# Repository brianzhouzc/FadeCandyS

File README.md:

# FadeCandy S

FadeCandyS, which stands for FadeCandy Slim, is a modified version of the original [FadeCandy](https://github.com/scanlime/fadecandy) by scanlime. It's designed to be the same width as an [Adafruit NeoPixel Stick](https://www.adafruit.com/product/1426) and can be directly soldered onto the back of the NeoPixel Stick. It only uses one pin instead of the 8 pins on the original FadeCandy, thus is only capable of controlling 64LEDs maximum.

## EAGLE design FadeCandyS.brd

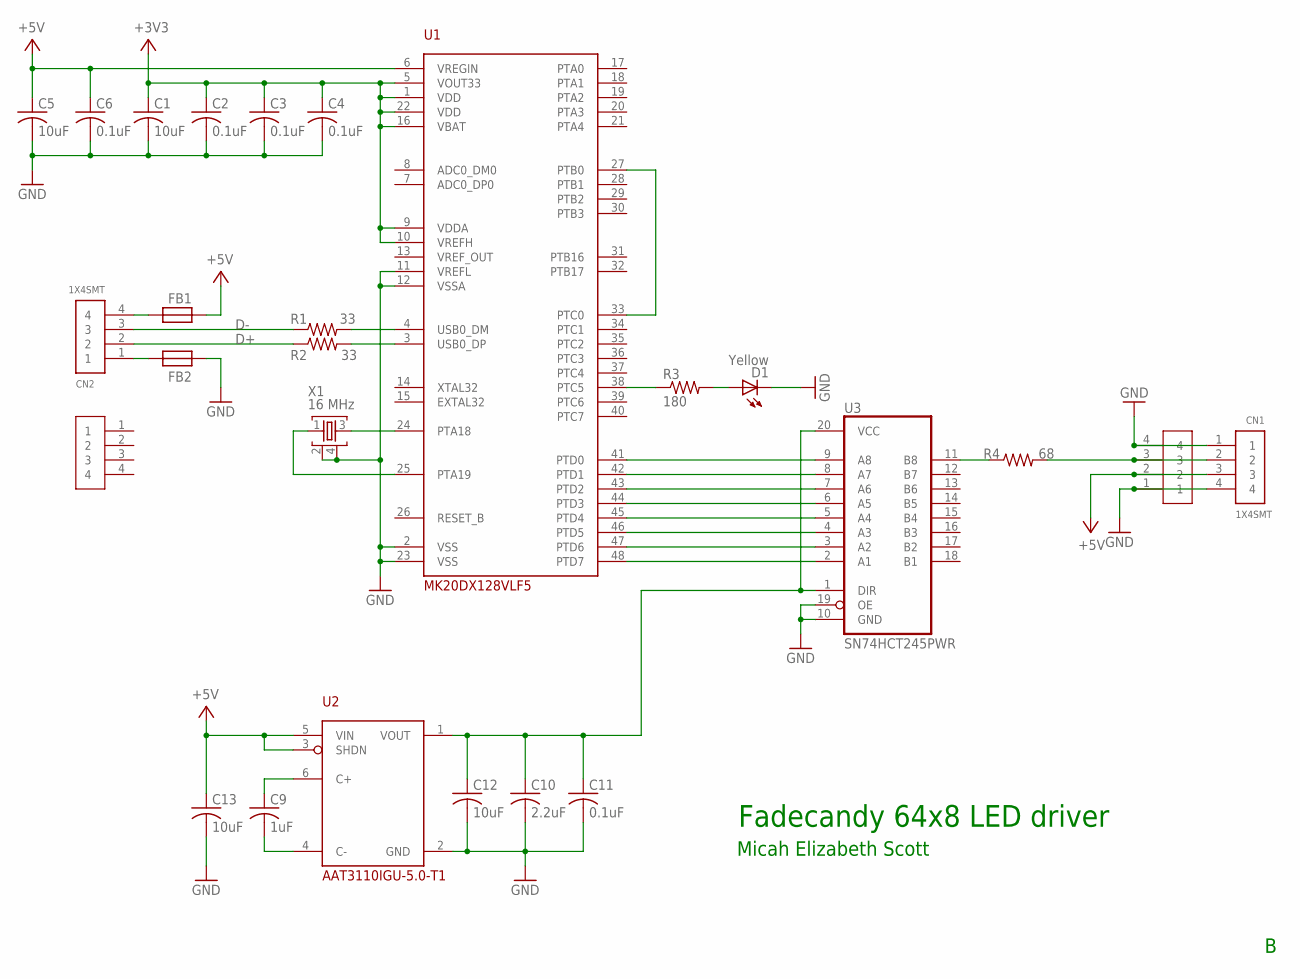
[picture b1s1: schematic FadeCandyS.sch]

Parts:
1X4_HALFVIA: 1X4_HALFVIA
C1, C5, C12, C13: 10uF; 0805
C2, C3, C4, C6, C11: 0.1uF; 0805
C9: 1uF; 0805
C10: 2.2uF; 0805
CN1, CN2: 1X4SMT; 1X4-SMT
D1: Yellow; CHIP-LED0805
FB1, FB2: FB0805/NO-OUTLINE; 0805
R1, R2: 33; 0805
R3: 180; 0805
R4: 68; 0805
U1: MK20DX128VLF5; LQFP48
U2: AAT3110IGU-5.0-T1; SOT23-6L
U3: SN74HCT245PWR; TSSOP20
U$1: 1X4_HALFVIA
X1: 16 MHz; TSX-3225

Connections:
+3V3: C1.1, C2.1, C3.1, C4.1, U1.1 (VDD), U1.5 (VOUT33), U1.9 (VDDA), U1.10 (VREFH), U1.16 (VBAT), U1.22 (VDD)
+5V: 1X4_HALFVIA.2, C5.1, C6.1, C13.1, CN1.3, FB1.2, U1.6 (VREGIN), U2.3 (SHDN), U2.5 (VIN)
D+: CN2.2, R2.1
D-: CN2.3, R1.1
GND: 1X4_HALFVIA.1, 1X4_HALFVIA.4, C1.2, C2.2, C3.2, C4.2, C5.2, C6.2, C10.2, C11.2, C12.2, C13.2, CN1.1, CN1.4, D1.C, FB2.2, U1.2 (VSS), U1.11 (VREFL), U1.12 (VSSA), U1.23 (VSS), U2.2 (GND), U3.10 (GND), U3.19 (OE), X1.2, X1.4
unnamed: R3.1, U1.38 (PTC5)
unnamed: U1.24 (PTA18), X1.3
unnamed: D1.A, R3.2
unnamed: U1.25 (PTA19), X1.1
unnamed: CN2.4, FB1.1
unnamed: U1.27 (PTB0), U1.33 (PTC0)
unnamed: CN2.1, FB2.1
unnamed: U1.41 (PTD0), U3.9 (A8)
unnamed: 1X4_HALFVIA.3, CN1.2, R4.2
unnamed: R1.2, U1.4 (USB0_DM)
unnamed: R2.2, U1.3 (USB0_DP)
unnamed: U1.42 (PTD1), U3.8 (A7)
unnamed: U1.43 (PTD2), U3.7 (A6)
unnamed: U1.44 (PTD3), U3.6 (A5)
unnamed: U1.45 (PTD4), U3.5 (A4)
unnamed: U1.46 (PTD5), U3.4 (A3)
unnamed: U1.47 (PTD6), U3.3 (A2)
unnamed: U1.48 (PTD7), U3.2 (A1)
unnamed: R4.1, U3.11 (B8)
unnamed: C9.1, U2.6 (C+)
unnamed: C9.2, U2.4 (C-)
unnamed: C10.1, C11.1, C12.1, U2.1 (VOUT), U3.1 (DIR), U3.20 (VCC)

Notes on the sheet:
Fadecandy 64x8 LED driver
Micah Elizabeth Scott

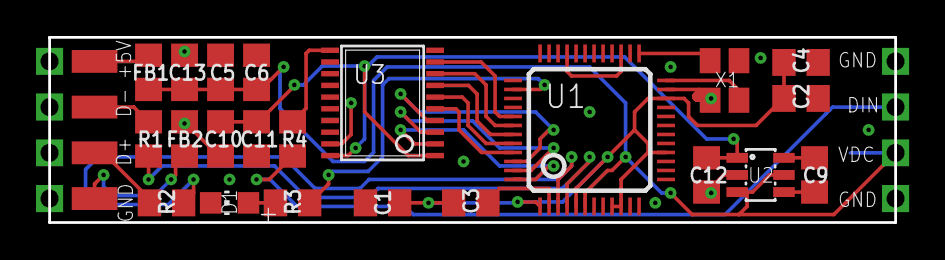
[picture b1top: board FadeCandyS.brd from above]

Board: 2 copper layers, 47.0 x 10.3 mm, 26 parts (1 on the bottom side), 27 nets.

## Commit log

2018-09-29 Added images
2018-09-29 Create LICENSE
